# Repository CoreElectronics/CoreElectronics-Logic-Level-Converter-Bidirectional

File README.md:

# Core Electronics Logic Level Converter Bidirectional, 4 Channel

This [Bi-Directional Logic Level Converter](https://core-electronics.com.au/catalog/product/view/sku/CE07510) is a breadboard-friendly device that converts between eg. 5V and 3.3V logic. The four channels are independent and work in both directions, making this converter appropriate for shifting I2C bus voltages.

Power the board from the two voltage sources you're using. Connect the higher voltage (eg. 5V) to the 'HV' power pin, the lower voltage (eg. 3.3V) to the 'LV' power pin, and the ground to the 'GND' pin.

Features:

- 4 independent channels
- Breadboard friendly - just bring your own [pin headers](https://core-electronics.com.au/catalog/product/view/sku/FIT0084)
- Small size (15x13mm)
- Manufactured and [supported](https://core-electronics.com.au/contacts/) in Australia by Core Electronics

# License
This project is open source - please review the LICENSE.md file for further licensing information.

If you have any technical questions, or concerns about licensing, please contact technical support on the [Core Electronics forums](https://forum.core-electronics.com.au/).

# Attribution
The hardware design of this module is influenced by the design from [Sparkfun](https://github.com/sparkfun/Logic_Level_Bidirectional).

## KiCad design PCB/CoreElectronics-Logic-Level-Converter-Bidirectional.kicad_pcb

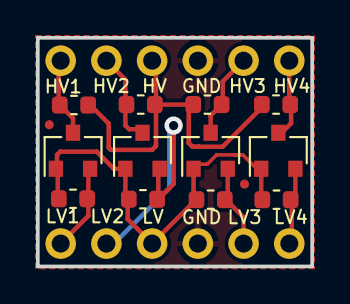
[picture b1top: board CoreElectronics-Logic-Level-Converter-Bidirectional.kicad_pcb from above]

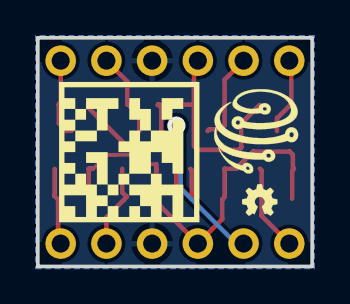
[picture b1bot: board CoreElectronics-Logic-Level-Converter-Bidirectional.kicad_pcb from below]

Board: 2 copper layers, 15.2 x 12.7 mm, 19 parts (5 on the bottom side), 11 nets.

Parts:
G1: LOGO; core-logo
G2: LOGO_made-with-love; CE07510
JP1: LV; PinHeader_1x06_P2.54mm_Vertical
JP2, JP3: FIDUCIALUFIDUCIAL; Fiducial_0.5mm_Mask1mm
JP4: HV; PinHeader_1x06_P2.54mm_Vertical
LOGO1: Logo_Open_Hardware_Small; oshw
Q1, Q2, Q3, Q4: BSS138; SOT-23
R1, R2, R3, R4, R5, R6, R7, R8: 10K; R_0603_1608Metric

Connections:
/GND: JP1.3, JP4.4
/HV1: JP4.1, Q1.3 (D), R2.2
/HV2: JP4.2, Q2.3 (D), R4.2
/HV3: JP4.5, Q3.3 (D), R6.2
/HV4: JP4.6, Q4.3 (D), R8.2
/LV1: JP1.6, Q1.2 (S), R1.2
/LV2: JP1.5, Q2.2 (S), R3.2
/LV3: JP1.2, Q3.2 (S), R5.2
/LV4: JP1.1, Q4.2 (S), R7.2
HV: JP4.3, R2.1, R4.1, R6.1, R8.1
LV: JP1.4, Q1.1 (G), Q2.1 (G), Q3.1 (G), Q4.1 (G), R1.1, R3.1, R5.1, R7.1

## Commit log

2022-10-28 update design with datamatrix
2022-11-07 cleanup project
